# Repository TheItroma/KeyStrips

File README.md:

# KeyStrips

After a bit of research (this)[https://github.com/Ghgore/handwire-pcbs] came up.
This differs from that where as instead of singular switches, it is strips that
can be broken into singular switches. It has for main advantage over the amoeba
design(handwire-pcb is the repo name)

The KeyStrip design allows for :

- A hybrid between handwired and pcb
- Modularity
- RGB
- Very very low cost since you don't buy 3 pcb's you don't need and no space is
  wasted
- Making custom ergo keyboards sooo incredibly easy

Why would you make one custom if there are already so many out there? Because :
some people have weird hands and specific additional features such as specific
placements for particular modules.

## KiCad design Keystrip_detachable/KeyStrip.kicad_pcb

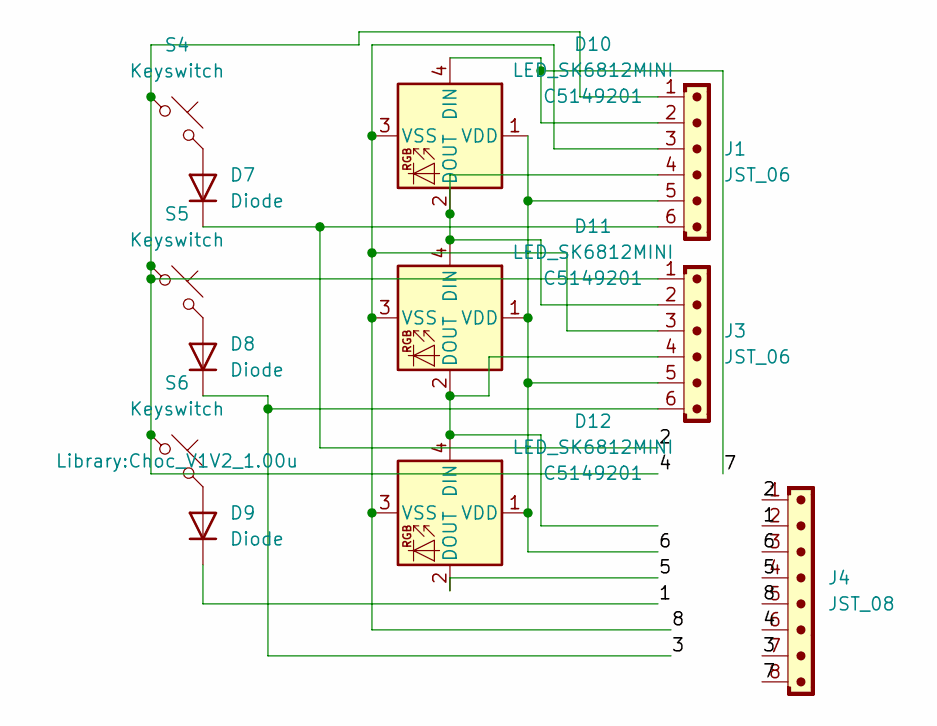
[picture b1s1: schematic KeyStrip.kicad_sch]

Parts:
D7, D8, D9: Diode; DualDiode
D10, D11, D12: LED_SK6812MINI; SK6812Mini-E; LCSC C5149201
J1, J3: JST_06; 6pin
J4: JST_08; JST_EH_B8B-EH-A_1x08_P2.50mm_Vertical
S4, S5, S6: Keyswitch; Choc_V1V2_1.00u

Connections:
/1: D9.1 (K), J4.2
/2: D7.1 (K), J1.6, J4.1
/3: D8.1 (K), J3.6, J4.7
/4: J1.1, J3.1, J4.6, S4.1, S5.1, S6.1
/5: D12.2 (DOUT), J4.4
/6: D10.1 (VDD), D11.1 (VDD), D12.1 (VDD), J1.5, J3.5, J4.3
/7: D10.4 (DIN), J1.2, J4.8
/8: D10.3 (VSS), D11.3 (VSS), D12.3 (VSS), J1.3, J3.3, J4.5
unnamed: D7.2 (A), S4.2
unnamed: D8.2 (A), S5.2
unnamed: D9.2 (A), S6.2
unnamed: D10.2 (DOUT), D11.4 (DIN), J1.4, J3.2
unnamed: D11.2 (DOUT), D12.4 (DIN), J3.4

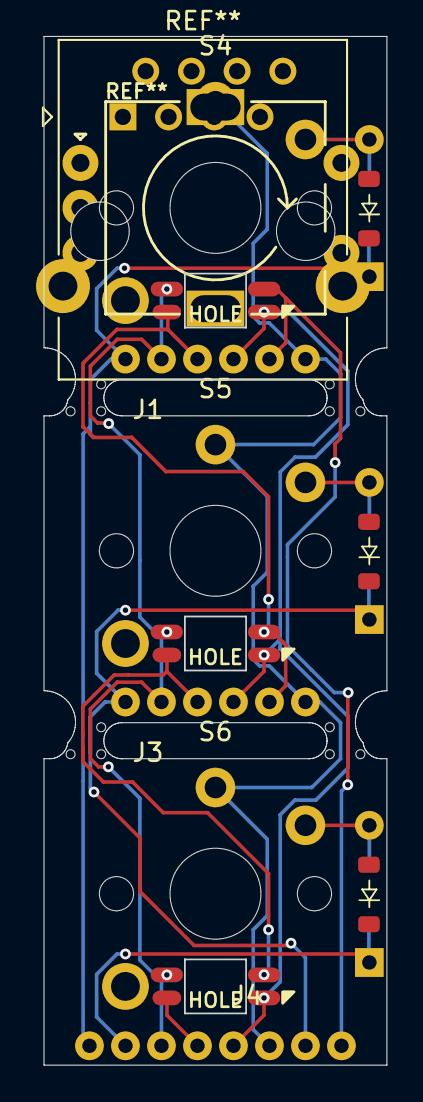
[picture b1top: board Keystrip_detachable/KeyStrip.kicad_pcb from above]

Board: 2 copper layers, 19.1 x 57.2 mm, 12 parts (0 on the bottom side), 13 nets.

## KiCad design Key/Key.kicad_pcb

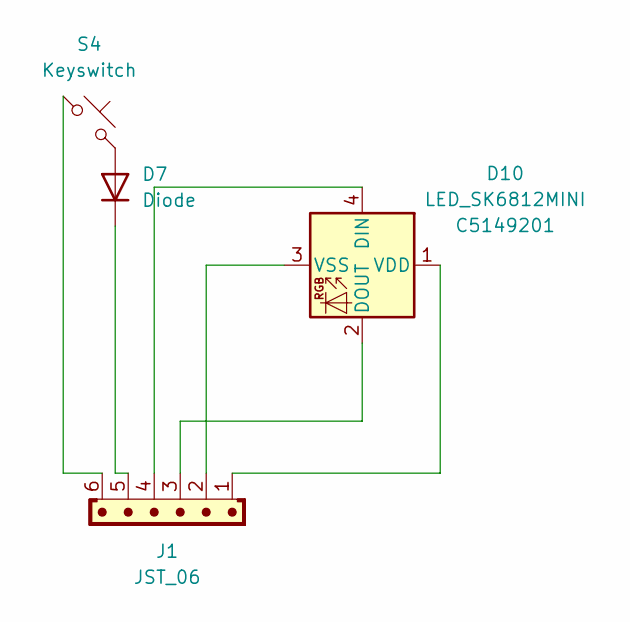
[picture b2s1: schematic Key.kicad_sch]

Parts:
D7: Diode; DualDiode
D10: LED_SK6812MINI; SK6812Mini-E; LCSC C5149201
J1: JST_06; JST_EH_B8B-EH-A_1x08_P2.50mm_Vertical_copy
S4: Keyswitch; Choc_V1V2_1.00u

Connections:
unnamed: D7.2 (A), S4.2
unnamed: D7.1 (K), J1.5
unnamed: D10.4 (DIN), J1.4
unnamed: D10.2 (DOUT), J1.3
unnamed: D10.1 (VDD), J1.1
unnamed: D10.3 (VSS), J1.2
unnamed: J1.6, S4.1

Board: 2 copper layers, 4 parts (0 on the bottom side), 7 nets, no tracks yet.

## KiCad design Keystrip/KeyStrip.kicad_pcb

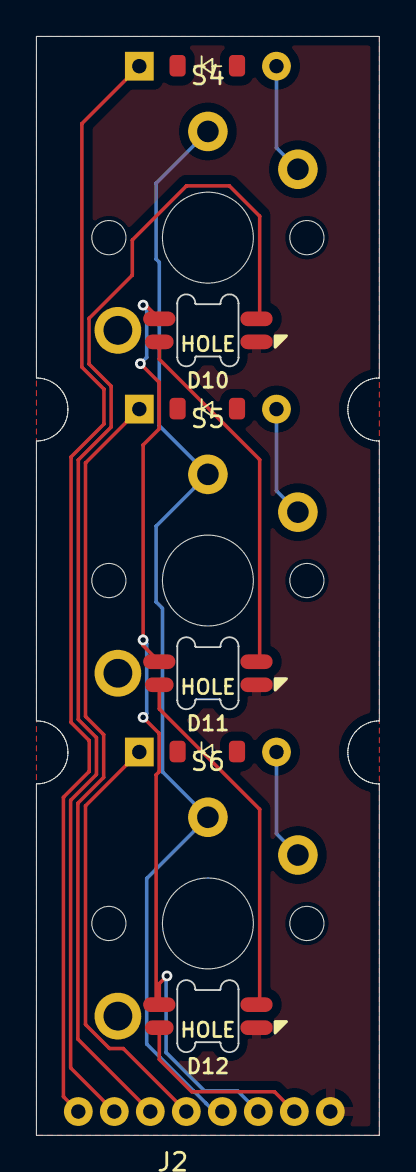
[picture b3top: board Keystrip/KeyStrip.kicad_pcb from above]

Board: 2 copper layers, 19.1 x 61.0 mm, 10 parts (0 on the bottom side), 13 nets.

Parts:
D7, D8, D9: Diode; DualDiode
D10, D11, D12: LED_SK6812MINI; SK6812Mini-E
J2: JST_08; JST_EH_B8B-EH-A_1x08_P2.50mm_Vertical
S4, S5, S6: Keyswitch; Choc_V1V2_1.00u

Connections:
unnamed: D7.2 (A), S4.2
unnamed: D7.1 (K), J2.8
unnamed: D8.2 (A), S5.2
unnamed: D8.1 (K), J2.6
unnamed: D9.2 (A), S6.2
unnamed: D9.1 (K), J2.5
unnamed: D10.4 (DIN), J2.7
unnamed: D10.2 (DOUT), D11.4 (DIN)
unnamed: D10.1 (VDD), D11.1 (VDD), D12.1 (VDD), J2.3
unnamed: D10.3 (VSS), D11.3 (VSS), D12.3 (VSS), J2.1
unnamed: D11.2 (DOUT), D12.4 (DIN)
unnamed: D12.2 (DOUT), J2.2
unnamed: J2.4, S4.1, S5.1, S6.1

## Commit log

2025-10-03 init
2025-10-03 Organisation
2025-10-03 readme
2025-10-15 Fixed a footprint and yeah thats it
2025-10-15 Actually well routed and placed this time
2025-10-18 I just gotta add screw holes and solo variations now
2025-10-18 Added screw holes and routed and fixed the thingy thing
2025-10-18 added gitignore and restructured a bit
2025-10-18 Added license
2025-10-18 Change license to CERN Open Hardware Licence V2
2025-10-18 restructured
2025-10-18 added detachable keys
2026-01-18 An 'artistic' routing job for sure
2026-01-20 uhhh, This feels both improved and weirder
2026-01-20 still artistic... Cleaner IG?
2026-01-25 hopefull it works, Sending to jlcpcb to get manifactured after this
